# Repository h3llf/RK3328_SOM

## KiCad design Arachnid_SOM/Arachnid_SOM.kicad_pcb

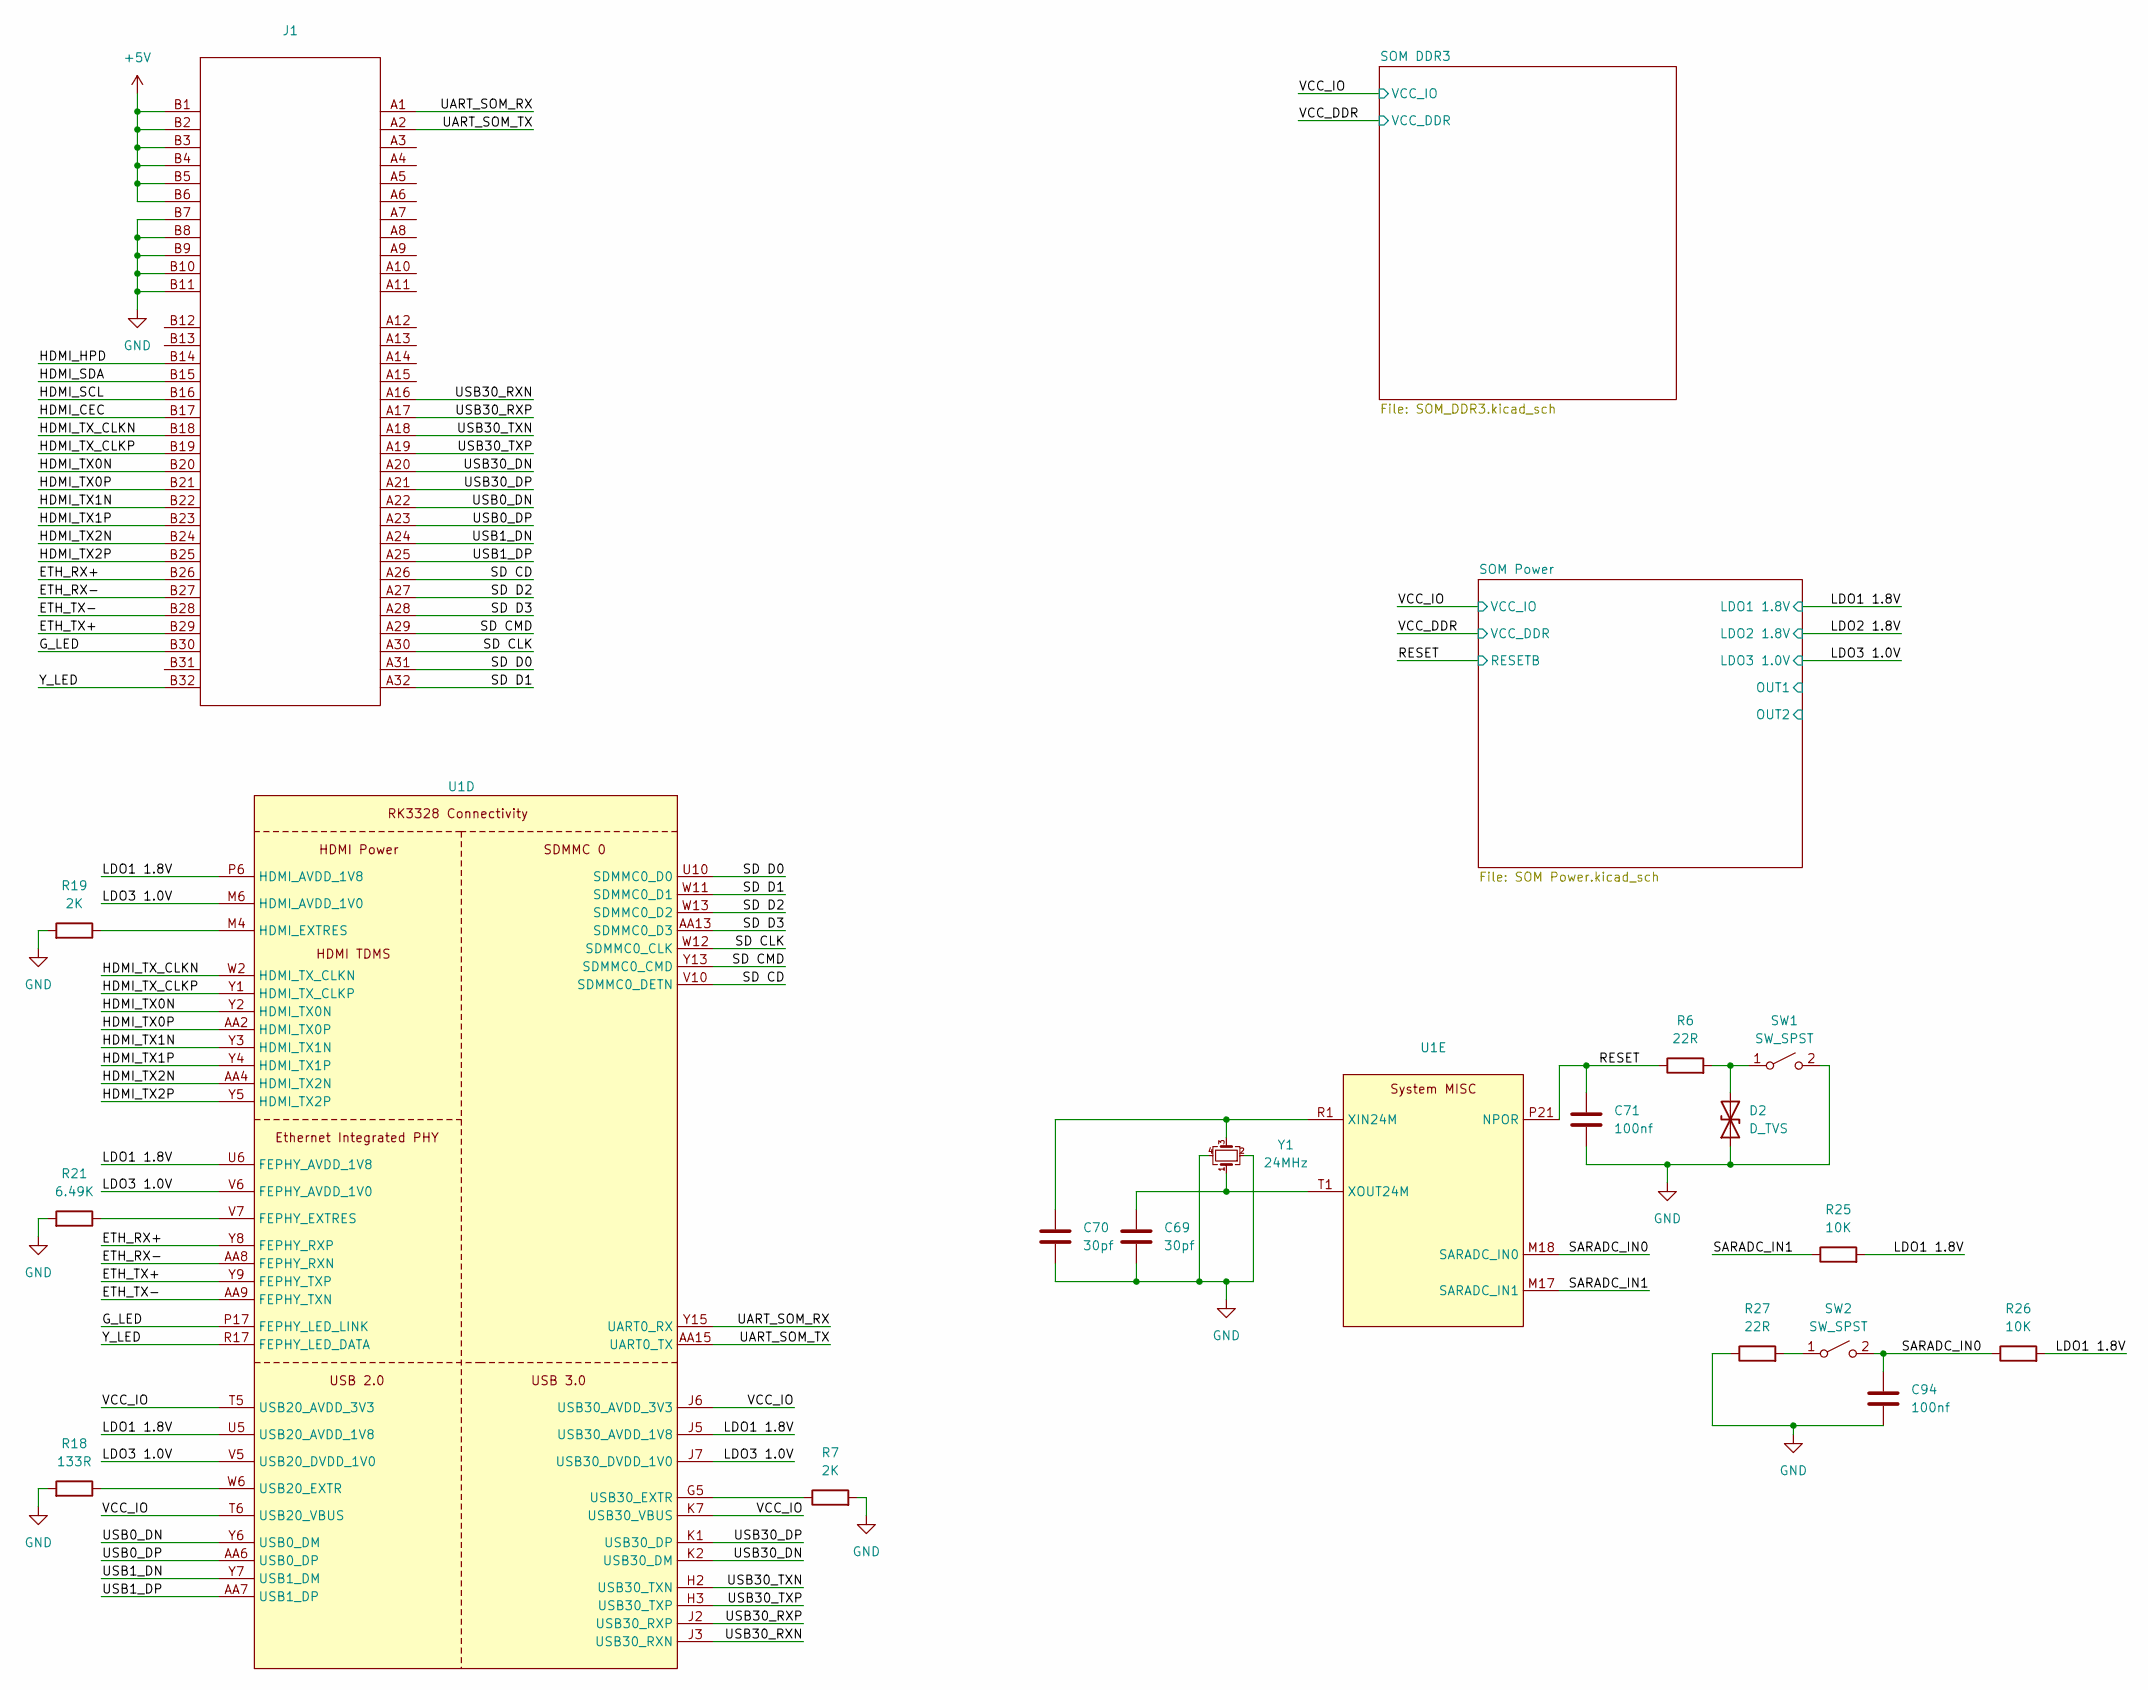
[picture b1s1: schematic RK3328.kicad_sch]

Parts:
C69, C70: 30pf; C_0402_1005Metric
C71, C94: 100nf; C_0402_1005Metric
D2: D_TVS; D_SOD-882
J1: BUS_PCIexpress_x4
R6, R27: 22R; R_0402_1005Metric
R7, R19: 2K; R_0402_1005Metric
R18: 133R; R_0402_1005Metric
R21: 6.49K; R_0402_1005Metric
R25, R26: 10K; R_0402_1005Metric
SW1, SW2: SW_SPST; SW_Push_1P1T_NO_Vertical_Wuerth_434133025816
U1: RK3328
Y1: 24MHz; Crystal_SMD_3225-4Pin_3.2x2.5mm; LCSC C70590

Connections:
+5V: J1.B1, J1.B2, J1.B3, J1.B4, J1.B5, J1.B6; also elsewhere on the board
/RK3328 SOM - DDR3 A/ETH_RX+: J1.B26, U1.Y8 (FEPHY_RXP)
/RK3328 SOM - DDR3 A/ETH_RX-: J1.B27, U1.AA8 (FEPHY_RXN)
/RK3328 SOM - DDR3 A/ETH_TX+: J1.B29, U1.Y9 (FEPHY_TXP)
/RK3328 SOM - DDR3 A/ETH_TX-: J1.B28, U1.AA9 (FEPHY_TXN)
/RK3328 SOM - DDR3 A/G_LED: J1.B30, U1.P17 (FEPHY_LED_LINK)
/RK3328 SOM - DDR3 A/HDMI_CEC: J1.B17
/RK3328 SOM - DDR3 A/HDMI_HPD: J1.B14
/RK3328 SOM - DDR3 A/HDMI_SCL: J1.B16
/RK3328 SOM - DDR3 A/HDMI_SDA: J1.B15
/RK3328 SOM - DDR3 A/HDMI_TX0N: J1.B20, U1.Y2 (HDMI_TX0N)
/RK3328 SOM - DDR3 A/HDMI_TX0P: J1.B21, U1.AA2 (HDMI_TX0P)
/RK3328 SOM - DDR3 A/HDMI_TX1N: J1.B22, U1.Y3 (HDMI_TX1N)
/RK3328 SOM - DDR3 A/HDMI_TX1P: J1.B23, U1.Y4 (HDMI_TX1P)
/RK3328 SOM - DDR3 A/HDMI_TX2N: J1.B24, U1.AA4 (HDMI_TX2N)
/RK3328 SOM - DDR3 A/HDMI_TX2P: J1.B25, U1.Y5 (HDMI_TX2P)
/RK3328 SOM - DDR3 A/HDMI_TX_CLKN: J1.B18, U1.W2 (HDMI_TX_CLKN)
/RK3328 SOM - DDR3 A/HDMI_TX_CLKP: J1.B19, U1.Y1 (HDMI_TX_CLKP)
/RK3328 SOM - DDR3 A/LDO1 1.8V: R25.2, R26.2, U1.J5 (USB30_AVDD_1V8), U1.P6 (HDMI_AVDD_1V8), U1.U5 (USB20_AVDD_1V8), U1.U6 (FEPHY_AVDD_1V8); also elsewhere on the board
/RK3328 SOM - DDR3 A/LDO3 1.0V: U1.J7 (USB30_DVDD_1V0), U1.M6 (HDMI_AVDD_1V0), U1.V5 (USB20_DVDD_1V0), U1.V6 (FEPHY_AVDD_1V0); also elsewhere on the board
/RK3328 SOM - DDR3 A/RESET: C71.1, R6.1, U1.P21 (NPOR)
/RK3328 SOM - DDR3 A/SARADC_IN0: C94.1, R26.1, SW2.2 (B), U1.M18 (SARADC_IN0)
/RK3328 SOM - DDR3 A/SARADC_IN1: R25.1, U1.M17 (SARADC_IN1)
/RK3328 SOM - DDR3 A/SD CD: J1.A26, U1.V10 (SDMMC0_DETN)
/RK3328 SOM - DDR3 A/SD CLK: J1.A30, U1.W12 (SDMMC0_CLK)
/RK3328 SOM - DDR3 A/SD CMD: J1.A29, U1.Y13 (SDMMC0_CMD)
/RK3328 SOM - DDR3 A/SD D0: J1.A31, U1.U10 (SDMMC0_D0)
/RK3328 SOM - DDR3 A/SD D1: J1.A32, U1.W11 (SDMMC0_D1)
/RK3328 SOM - DDR3 A/SD D2: J1.A27, U1.W13 (SDMMC0_D2)
/RK3328 SOM - DDR3 A/SD D3: J1.A28, U1.AA13 (SDMMC0_D3)
/RK3328 SOM - DDR3 A/UART_SOM_RX: J1.A1, U1.Y15 (UART0_RX)
/RK3328 SOM - DDR3 A/UART_SOM_TX: J1.A2, U1.AA15 (UART0_TX)
/RK3328 SOM - DDR3 A/USB0_DN: J1.A22, U1.Y6 (USB0_DM)
/RK3328 SOM - DDR3 A/USB0_DP: J1.A23, U1.AA6 (USB0_DP)
/RK3328 SOM - DDR3 A/USB1_DN: J1.A24, U1.Y7 (USB1_DM)
/RK3328 SOM - DDR3 A/USB1_DP: J1.A25, U1.AA7 (USB1_DP)
/RK3328 SOM - DDR3 A/USB30_DN: J1.A20, U1.K2 (USB30_DM)
/RK3328 SOM - DDR3 A/USB30_DP: J1.A21, U1.K1 (USB30_DP)
/RK3328 SOM - DDR3 A/USB30_RXN: J1.A16, U1.J3 (USB30_RXN)
/RK3328 SOM - DDR3 A/USB30_RXP: J1.A17, U1.J2 (USB30_RXP)
/RK3328 SOM - DDR3 A/USB30_TXN: J1.A18, U1.H2 (USB30_TXN)
/RK3328 SOM - DDR3 A/USB30_TXP: J1.A19, U1.H3 (USB30_TXP)
/RK3328 SOM - DDR3 A/VCC_IO: U1.J6 (USB30_AVDD_3V3), U1.K7 (USB30_VBUS), U1.T5 (USB20_AVDD_3V3), U1.T6 (USB20_VBUS); also elsewhere on the board
/RK3328 SOM - DDR3 A/Y_LED: J1.B32, U1.R17 (FEPHY_LED_DATA)
GND: C69.2, C70.2, C71.2, C94.2, D2.1 (A1), J1.B7, J1.B8, J1.B9, J1.B10, J1.B11, R7.2, R18.2, R19.2, R21.2, R27.1, SW1.2 (B), Y1.2, Y1.4; also elsewhere on the board
unnamed: D2.2 (A2), R6.2, SW1.1 (A)
unnamed: R27.2, SW2.1 (A)
unnamed: R21.1, U1.V7 (FEPHY_EXTRES)
unnamed: R19.1, U1.M4 (HDMI_EXTRES)
unnamed: R18.1, U1.W6 (USB20_EXTR)
unnamed: R7.1, U1.G5 (USB30_EXTR)
unnamed: C70.1, U1.R1 (XIN24M), Y1.3
unnamed: C69.1, U1.T1 (XOUT24M), Y1.1

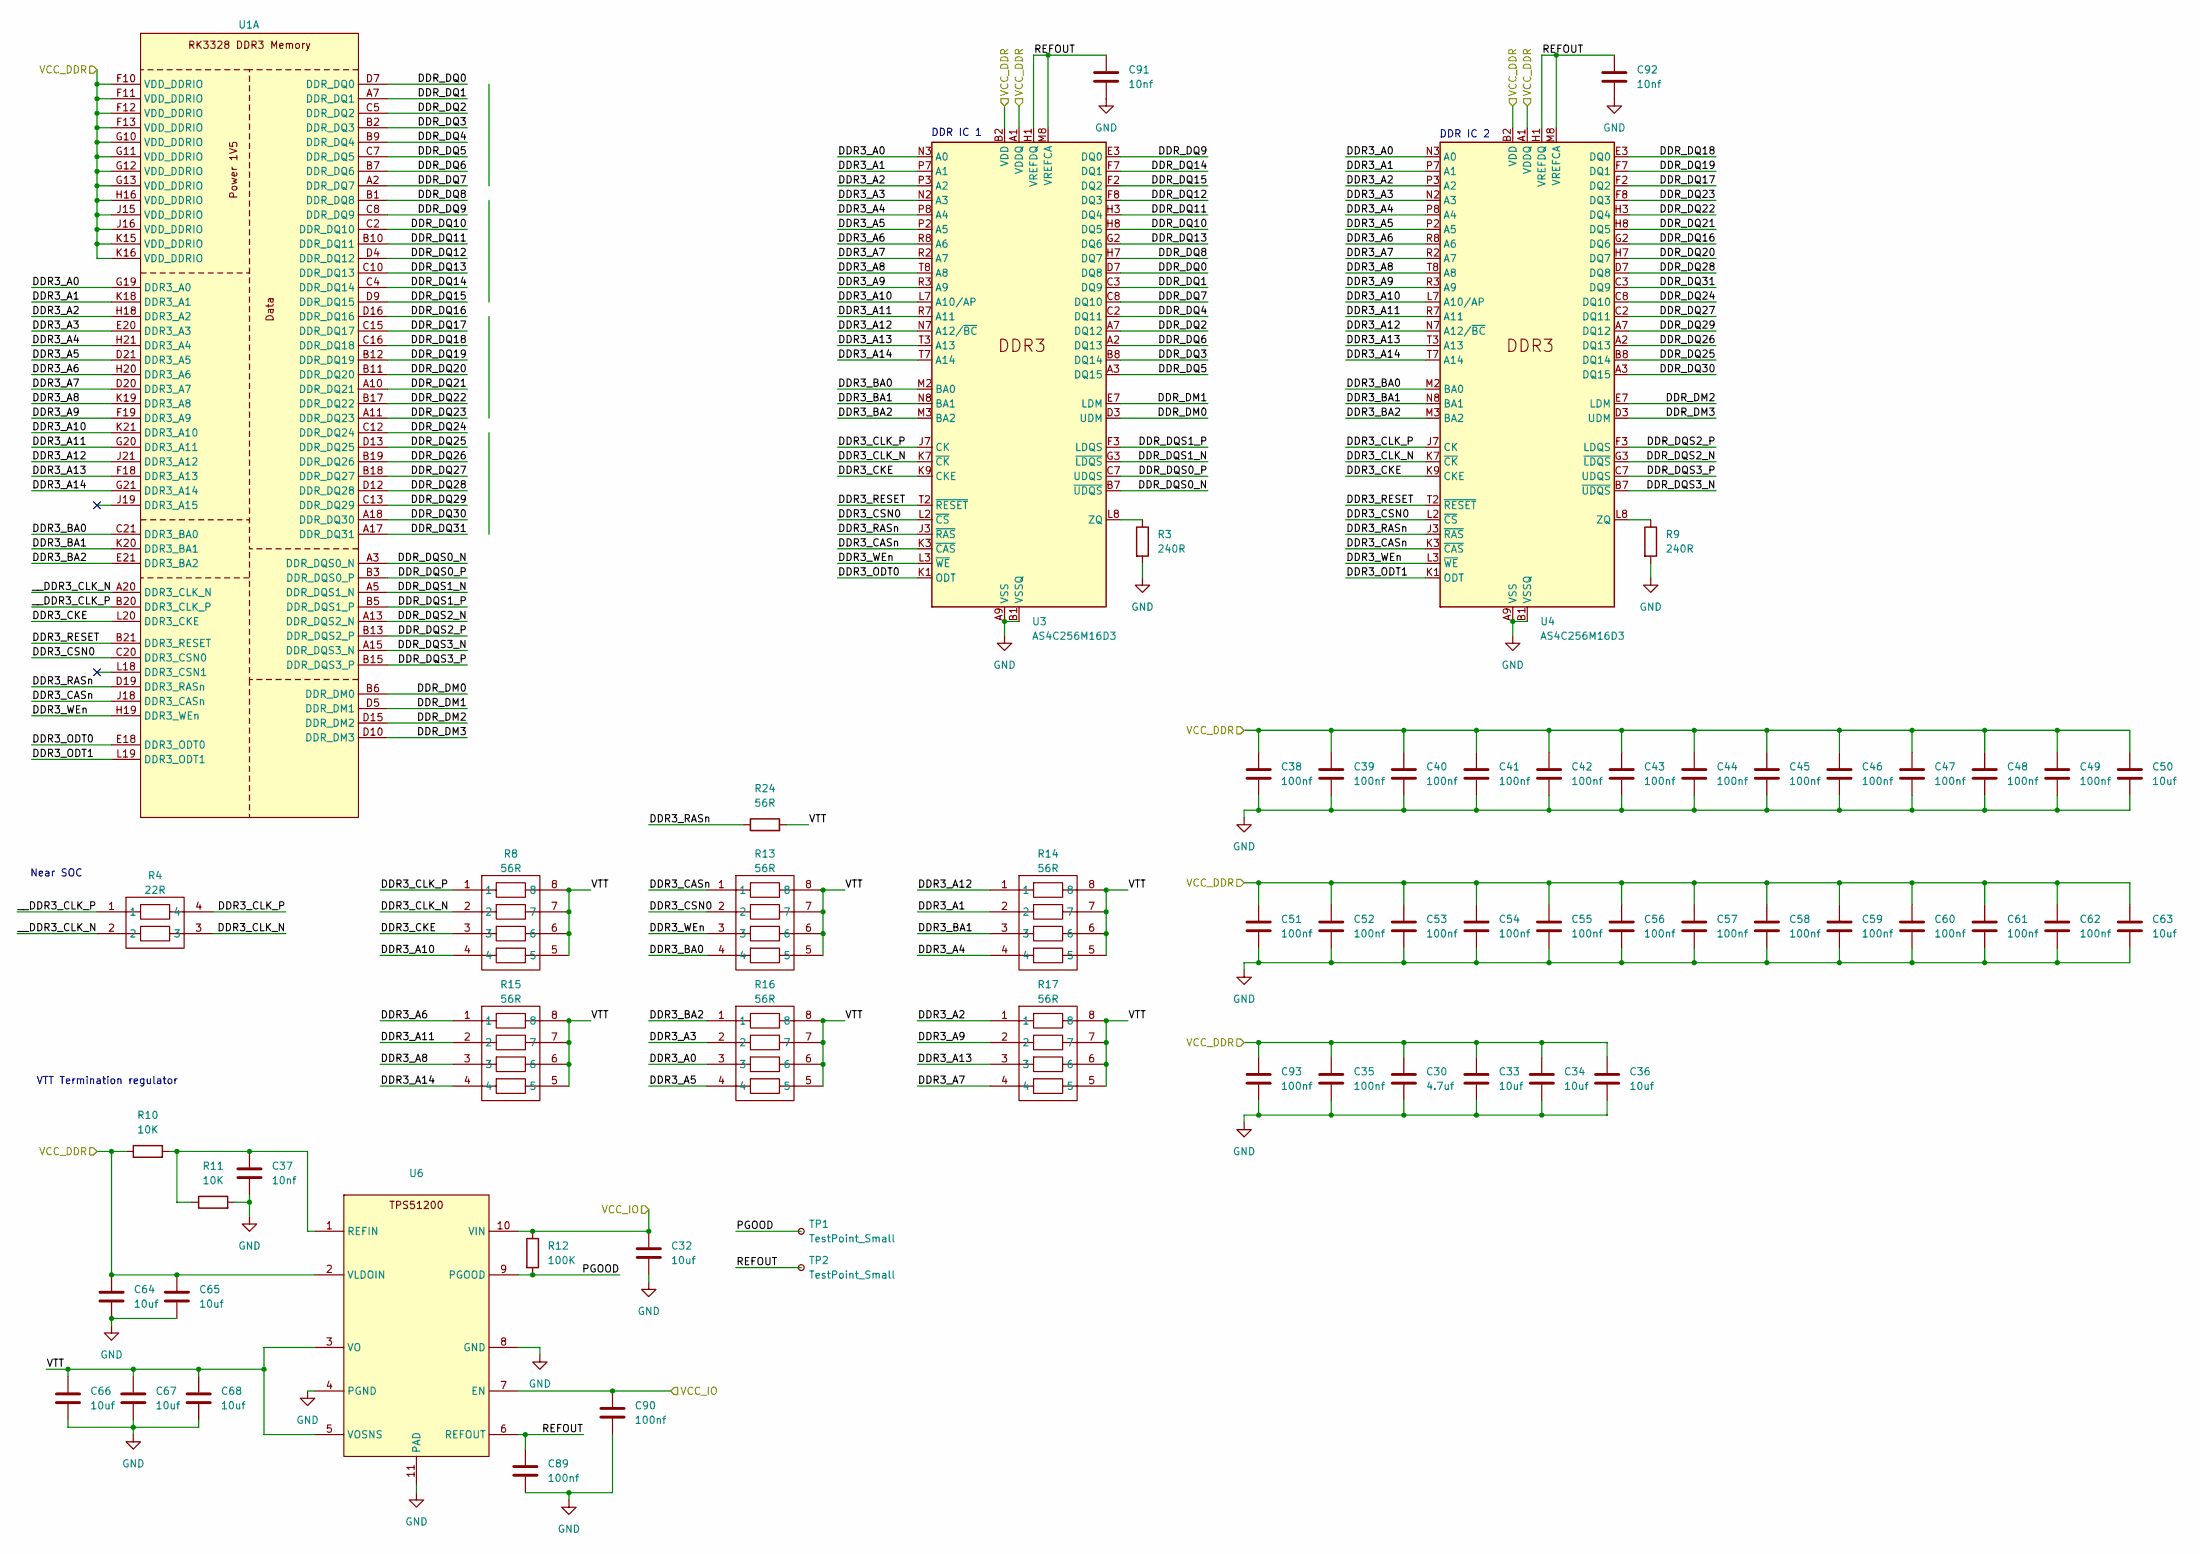
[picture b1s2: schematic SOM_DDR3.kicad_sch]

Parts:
C30: 4.7uf; C_0402_1005Metric
C32, C33, C34, C36, C50, C63, C64, C65, C66, C67, C68: 10uf; C_0402_1005Metric
C35, C38, C39, C40, C41, C42, C43, C44, C45, C46, C47, C48, C49, C51, C52, C53, C54, C55, C56, C57, C58, C59, C60, C61, C62, C89, C90, C93: 100nf; C_0402_1005Metric
C37, C91, C92: 10nf; C_0402_1005Metric
R3, R9: 240R; R_0402_1005Metric_Pad0.72x0.64mm_HandSolder
R4: 22R; R_Array_Convex_2x0402
R8, R13, R14, R15, R16, R17: 56R; R_Array_Convex_4x0402
R10, R11: 10K; R_0402_1005Metric
R12: 100K; R_0402_1005Metric
R24: 56R; R_0402_1005Metric
TP1, TP2: TestPoint_Small; TestPoint_Pad_D1.5mm
U1: RK3328
U3, U4: AS4C256M16D3; BGA-96_9.0x13.0mm_Layout2x3x16_P0.8mm
U6: VSON-10-1EP_3x3mm_P0.5mm_EP1.65x2.4mm_ThermalVias

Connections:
/RK3328 SOM - DDR3 A/SOM DDR3/DDR3_A0: R16.3, U1.G19 (DDR3_A0), U3.N3 (A0), U4.N3 (A0)
/RK3328 SOM - DDR3 A/SOM DDR3/DDR3_A1: R14.2, U1.K18 (DDR3_A1), U3.P7 (A1), U4.P7 (A1)
/RK3328 SOM - DDR3 A/SOM DDR3/DDR3_A2: R17.1, U1.H18 (DDR3_A2), U3.P3 (A2), U4.P3 (A2)
/RK3328 SOM - DDR3 A/SOM DDR3/DDR3_A3: R16.2, U1.E20 (DDR3_A3), U3.N2 (A3), U4.N2 (A3)
/RK3328 SOM - DDR3 A/SOM DDR3/DDR3_A4: R14.4, U1.H21 (DDR3_A4), U3.P8 (A4), U4.P8 (A4)
/RK3328 SOM - DDR3 A/SOM DDR3/DDR3_A5: R16.4, U1.D21 (DDR3_A5), U3.P2 (A5), U4.P2 (A5)
/RK3328 SOM - DDR3 A/SOM DDR3/DDR3_A6: R15.1, U1.H20 (DDR3_A6), U3.R8 (A6), U4.R8 (A6)
/RK3328 SOM - DDR3 A/SOM DDR3/DDR3_A7: R17.4, U1.D20 (DDR3_A7), U3.R2 (A7), U4.R2 (A7)
/RK3328 SOM - DDR3 A/SOM DDR3/DDR3_A8: R15.3, U1.K19 (DDR3_A8), U3.T8 (A8), U4.T8 (A8)
/RK3328 SOM - DDR3 A/SOM DDR3/DDR3_A9: R17.2, U1.F19 (DDR3_A9), U3.R3 (A9), U4.R3 (A9)
/RK3328 SOM - DDR3 A/SOM DDR3/DDR3_A10: R8.4, U1.K21 (DDR3_A10), U3.L7 (A10/AP), U4.L7 (A10/AP)
/RK3328 SOM - DDR3 A/SOM DDR3/DDR3_A11: R15.2, U1.G20 (DDR3_A11), U3.R7 (A11), U4.R7 (A11)
/RK3328 SOM - DDR3 A/SOM DDR3/DDR3_A12: R14.1, U1.J21 (DDR3_A12), U3.N7 (A12/~BC), U4.N7 (A12/~BC)
/RK3328 SOM - DDR3 A/SOM DDR3/DDR3_A13: R17.3, U1.F18 (DDR3_A13), U3.T3 (A13), U4.T3 (A13)
/RK3328 SOM - DDR3 A/SOM DDR3/DDR3_A14: R15.4, U1.G21 (DDR3_A14), U3.T7 (A14), U4.T7 (A14)
/RK3328 SOM - DDR3 A/SOM DDR3/DDR3_BA0: R13.4, U1.C21 (DDR3_BA0), U3.M2 (BA0), U4.M2 (BA0)
/RK3328 SOM - DDR3 A/SOM DDR3/DDR3_BA1: R14.3, U1.K20 (DDR3_BA1), U3.N8 (BA1), U4.N8 (BA1)
/RK3328 SOM - DDR3 A/SOM DDR3/DDR3_BA2: R16.1, U1.E21 (DDR3_BA2), U3.M3 (BA2), U4.M3 (BA2)
/RK3328 SOM - DDR3 A/SOM DDR3/DDR3_CASn: R13.1, U1.J18 (DDR3_CASn), U3.K3 (~CAS), U4.K3 (~CAS)
/RK3328 SOM - DDR3 A/SOM DDR3/DDR3_CKE: R8.3, U1.L20 (DDR3_CKE), U3.K9 (CKE), U4.K9 (CKE)
/RK3328 SOM - DDR3 A/SOM DDR3/DDR3_CLK_N: R4.3, R8.2, U3.K7 (~CK), U4.K7 (~CK)
/RK3328 SOM - DDR3 A/SOM DDR3/DDR3_CLK_P: R4.4, R8.1, U3.J7 (CK), U4.J7 (CK)
/RK3328 SOM - DDR3 A/SOM DDR3/DDR3_CSN0: R13.2, U1.C20 (DDR3_CSN0), U3.L2 (~CS), U4.L2 (~CS)
/RK3328 SOM - DDR3 A/SOM DDR3/DDR3_ODT0: U1.E18 (DDR3_ODT0), U3.K1 (ODT)
/RK3328 SOM - DDR3 A/SOM DDR3/DDR3_ODT1: U1.L19 (DDR3_ODT1), U4.K1 (ODT)
/RK3328 SOM - DDR3 A/SOM DDR3/DDR3_RASn: R24.1, U1.D19 (DDR3_RASn), U3.J3 (~RAS), U4.J3 (~RAS)
/RK3328 SOM - DDR3 A/SOM DDR3/DDR3_RESET: U1.B21 (DDR3_RESET), U3.T2 (~RESET), U4.T2 (~RESET)
/RK3328 SOM - DDR3 A/SOM DDR3/DDR3_WEn: R13.3, U1.H19 (DDR3_WEn), U3.L3 (~WE), U4.L3 (~WE)
/RK3328 SOM - DDR3 A/SOM DDR3/DDR_DM0: U1.B6 (DDR_DM0), U3.D3 (UDM)
/RK3328 SOM - DDR3 A/SOM DDR3/DDR_DM1: U1.D5 (DDR_DM1), U3.E7 (LDM)
/RK3328 SOM - DDR3 A/SOM DDR3/DDR_DM2: U1.D15 (DDR_DM2), U4.E7 (LDM)
/RK3328 SOM - DDR3 A/SOM DDR3/DDR_DM3: U1.D10 (DDR_DM3), U4.D3 (UDM)
/RK3328 SOM - DDR3 A/SOM DDR3/DDR_DQ0: U1.D7 (DDR_DQ0), U3.D7 (DQ8)
/RK3328 SOM - DDR3 A/SOM DDR3/DDR_DQ1: U1.A7 (DDR_DQ1), U3.C3 (DQ9)
/RK3328 SOM - DDR3 A/SOM DDR3/DDR_DQ2: U1.C5 (DDR_DQ2), U3.A7 (DQ12)
/RK3328 SOM - DDR3 A/SOM DDR3/DDR_DQ3: U1.B2 (DDR_DQ3), U3.B8 (DQ14)
/RK3328 SOM - DDR3 A/SOM DDR3/DDR_DQ4: U1.B9 (DDR_DQ4), U3.C2 (DQ11)
/RK3328 SOM - DDR3 A/SOM DDR3/DDR_DQ5: U1.C7 (DDR_DQ5), U3.A3 (DQ15)
/RK3328 SOM - DDR3 A/SOM DDR3/DDR_DQ6: U1.B7 (DDR_DQ6), U3.A2 (DQ13)
/RK3328 SOM - DDR3 A/SOM DDR3/DDR_DQ7: U1.A2 (DDR_DQ7), U3.C8 (DQ10)
/RK3328 SOM - DDR3 A/SOM DDR3/DDR_DQ8: U1.B1 (DDR_DQ8), U3.H7 (DQ7)
/RK3328 SOM - DDR3 A/SOM DDR3/DDR_DQ9: U1.C8 (DDR_DQ9), U3.E3 (DQ0)
/RK3328 SOM - DDR3 A/SOM DDR3/DDR_DQ10: U1.C2 (DDR_DQ10), U3.H8 (DQ5)
/RK3328 SOM - DDR3 A/SOM DDR3/DDR_DQ11: U1.B10 (DDR_DQ11), U3.H3 (DQ4)
/RK3328 SOM - DDR3 A/SOM DDR3/DDR_DQ12: U1.D4 (DDR_DQ12), U3.F8 (DQ3)
/RK3328 SOM - DDR3 A/SOM DDR3/DDR_DQ13: U1.C10 (DDR_DQ13), U3.G2 (DQ6)
/RK3328 SOM - DDR3 A/SOM DDR3/DDR_DQ14: U1.C4 (DDR_DQ14), U3.F7 (DQ1)
/RK3328 SOM - DDR3 A/SOM DDR3/DDR_DQ15: U1.D9 (DDR_DQ15), U3.F2 (DQ2)
/RK3328 SOM - DDR3 A/SOM DDR3/DDR_DQ16: U1.D16 (DDR_DQ16), U4.G2 (DQ6)
/RK3328 SOM - DDR3 A/SOM DDR3/DDR_DQ17: U1.C15 (DDR_DQ17), U4.F2 (DQ2)
/RK3328 SOM - DDR3 A/SOM DDR3/DDR_DQ18: U1.C16 (DDR_DQ18), U4.E3 (DQ0)
/RK3328 SOM - DDR3 A/SOM DDR3/DDR_DQ19: U1.B12 (DDR_DQ19), U4.F7 (DQ1)
/RK3328 SOM - DDR3 A/SOM DDR3/DDR_DQ20: U1.B11 (DDR_DQ20), U4.H7 (DQ7)
/RK3328 SOM - DDR3 A/SOM DDR3/DDR_DQ21: U1.A10 (DDR_DQ21), U4.H8 (DQ5)
/RK3328 SOM - DDR3 A/SOM DDR3/DDR_DQ22: U1.B17 (DDR_DQ22), U4.H3 (DQ4)
/RK3328 SOM - DDR3 A/SOM DDR3/DDR_DQ23: U1.A11 (DDR_DQ23), U4.F8 (DQ3)
/RK3328 SOM - DDR3 A/SOM DDR3/DDR_DQ24: U1.C12 (DDR_DQ24), U4.C8 (DQ10)
/RK3328 SOM - DDR3 A/SOM DDR3/DDR_DQ25: U1.D13 (DDR_DQ25), U4.B8 (DQ14)
/RK3328 SOM - DDR3 A/SOM DDR3/DDR_DQ26: U1.B19 (DDR_DQ26), U4.A2 (DQ13)
/RK3328 SOM - DDR3 A/SOM DDR3/DDR_DQ27: U1.B18 (DDR_DQ27), U4.C2 (DQ11)
/RK3328 SOM - DDR3 A/SOM DDR3/DDR_DQ28: U1.D12 (DDR_DQ28), U4.D7 (DQ8)
/RK3328 SOM - DDR3 A/SOM DDR3/DDR_DQ29: U1.C13 (DDR_DQ29), U4.A7 (DQ12)
/RK3328 SOM - DDR3 A/SOM DDR3/DDR_DQ30: U1.A18 (DDR_DQ30), U4.A3 (DQ15)
/RK3328 SOM - DDR3 A/SOM DDR3/DDR_DQ31: U1.A17 (DDR_DQ31), U4.C3 (DQ9)
/RK3328 SOM - DDR3 A/SOM DDR3/DDR_DQS0_N: U1.A3 (DDR_DQS0_N), U3.B7 (~UDQS)
/RK3328 SOM - DDR3 A/SOM DDR3/DDR_DQS0_P: U1.B3 (DDR_DQS0_P), U3.C7 (UDQS)
/RK3328 SOM - DDR3 A/SOM DDR3/DDR_DQS1_N: U1.A5 (DDR_DQS1_N), U3.G3 (~LDQS)
/RK3328 SOM - DDR3 A/SOM DDR3/DDR_DQS1_P: U1.B5 (DDR_DQS1_P), U3.F3 (LDQS)
/RK3328 SOM - DDR3 A/SOM DDR3/DDR_DQS2_N: U1.A13 (DDR_DQS2_N), U4.G3 (~LDQS)
/RK3328 SOM - DDR3 A/SOM DDR3/DDR_DQS2_P: U1.B13 (DDR_DQS2_P), U4.F3 (LDQS)
/RK3328 SOM - DDR3 A/SOM DDR3/DDR_DQS3_N: U1.A15 (DDR_DQS3_N), U4.B7 (~UDQS)
/RK3328 SOM - DDR3 A/SOM DDR3/DDR_DQS3_P: U1.B15 (DDR_DQS3_P), U4.C7 (UDQS)
/RK3328 SOM - DDR3 A/SOM DDR3/PGOOD: R12.2, TP1.1, U6.9 (PGOOD)
/RK3328 SOM - DDR3 A/SOM DDR3/REFOUT: C89.1, C91.1, C92.1, TP2.1, U3.H1 (VREFDQ), U3.M8 (VREFCA), U4.H1 (VREFDQ), U4.M8 (VREFCA), U6.6 (REFOUT)
/RK3328 SOM - DDR3 A/SOM DDR3/VTT: C66.1, C67.1, C68.1, R8.5, R8.6, R8.7, R8.8, R13.5, R13.6, R13.7, R13.8, R14.5, R14.6, R14.7, R14.8, R15.5, R15.6, R15.7, R15.8, R16.5, R16.6, R16.7, R16.8, R17.5, R17.6, R17.7, R17.8, R24.2, U6.3 (VO), U6.5 (VOSNS)
/RK3328 SOM - DDR3 A/SOM DDR3/__DDR3_CLK_N: R4.2, U1.A20 (DDR3_CLK_N)
/RK3328 SOM - DDR3 A/SOM DDR3/__DDR3_CLK_P: R4.1, U1.B20 (DDR3_CLK_P)
/RK3328 SOM - DDR3 A/VCC_DDR: C30.1, C33.1, C34.1, C35.1, C36.1, C38.1, C39.1, C40.1, C41.1, C42.1, C43.1, C44.1, C45.1, C46.1, C47.1, C48.1, C49.1, C50.1, C51.1, C52.1, C53.1, C54.1, C55.1, C56.1, C57.1, C58.1, C59.1, C60.1, C61.1, C62.1, C63.1, C64.1, C65.1, C93.1, R10.1, U1.F10 (VDD_DDRIO), U1.F11 (VDD_DDRIO), U1.F12 (VDD_DDRIO), U1.F13 (VDD_DDRIO), U1.G10 (VDD_DDRIO), U1.G11 (VDD_DDRIO), U1.G12 (VDD_DDRIO), U1.G13 (VDD_DDRIO), U1.H16 (VDD_DDRIO), U1.J15 (VDD_DDRIO), U1.J16 (VDD_DDRIO), U1.K15 (VDD_DDRIO), U1.K16 (VDD_DDRIO), U3.A1 (VDDQ), U3.A8 (VDDQ), U3.B2 (VDD), U3.C1 (VDDQ), U3.C9 (VDDQ), U3.D2 (VDDQ), U3.D9 (VDD), U3.E9 (VDDQ), U3.F1 (VDDQ), U3.G7 (VDD), U3.H2 (VDDQ), U3.H9 (VDDQ), U3.K2 (VDD), U3.K8 (VDD), U3.N1 (VDD), U3.N9 (VDD), U3.R1 (VDD), U3.R9 (VDD), U4.A1 (VDDQ), U4.A8 (VDDQ), U4.B2 (VDD), U4.C1 (VDDQ), U4.C9 (VDDQ), U4.D2 (VDDQ), U4.D9 (VDD), U4.E9 (VDDQ), U4.F1 (VDDQ), U4.G7 (VDD), U4.H2 (VDDQ), U4.H9 (VDDQ), U4.K2 (VDD), U4.K8 (VDD), U4.N1 (VDD), U4.N9 (VDD), U4.R1 (VDD), U4.R9 (VDD), U6.2 (VLDOIN); also elsewhere on the board
/RK3328 SOM - DDR3 A/VCC_IO: C32.1, C90.1, R12.1, U6.7 (EN), U6.10 (VIN); also elsewhere on the board
GND: C30.2, C32.2, C33.2, C34.2, C35.2, C36.2, C37.2, C38.2, C39.2, C40.2, C41.2, C42.2, C43.2, C44.2, C45.2, C46.2, C47.2, C48.2, C49.2, C50.2, C51.2, C52.2, C53.2, C54.2, C55.2, C56.2, C57.2, C58.2, C59.2, C60.2, C61.2, C62.2, C63.2, C64.2, C65.2, C66.2, C67.2, C68.2, C89.2, C90.2, C91.2, C92.2, C93.2, R3.2, R9.2, R11.2, U3.A9 (VSS), U3.B1 (VSSQ), U3.B3 (VSS), U3.B9 (VSSQ), U3.D1 (VSSQ), U3.D8 (VSSQ), U3.E1 (VSS), U3.E2 (VSSQ), U3.E8 (VSSQ), U3.F9 (VSSQ), U3.G1 (VSSQ), U3.G8 (VSS), U3.G9 (VSSQ), U3.J2 (VSS), U3.J8 (VSS), U3.M1 (VSS), U3.M9 (VSS), U3.P1 (VSS), U3.P9 (VSS), U3.T1 (VSS), U3.T9 (VSS), U4.A9 (VSS), U4.B1 (VSSQ), U4.B3 (VSS), U4.B9 (VSSQ), U4.D1 (VSSQ), U4.D8 (VSSQ), U4.E1 (VSS), U4.E2 (VSSQ), U4.E8 (VSSQ), U4.F9 (VSSQ), U4.G1 (VSSQ), U4.G8 (VSS), U4.G9 (VSSQ), U4.J2 (VSS), U4.J8 (VSS), U4.M1 (VSS), U4.M9 (VSS), U4.P1 (VSS), U4.P9 (VSS), U4.T1 (VSS), U4.T9 (VSS), U6.4 (PGND), U6.8 (GND), U6.11 (PAD); also elsewhere on the board
unnamed: R3.1, U3.L8 (ZQ)
unnamed: R9.1, U4.L8 (ZQ)
unnamed: C37.1, R10.2, R11.1, U6.1 (REFIN)

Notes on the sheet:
Near SOC
DDR IC 1
DDR IC 2
VTT Termination regulator

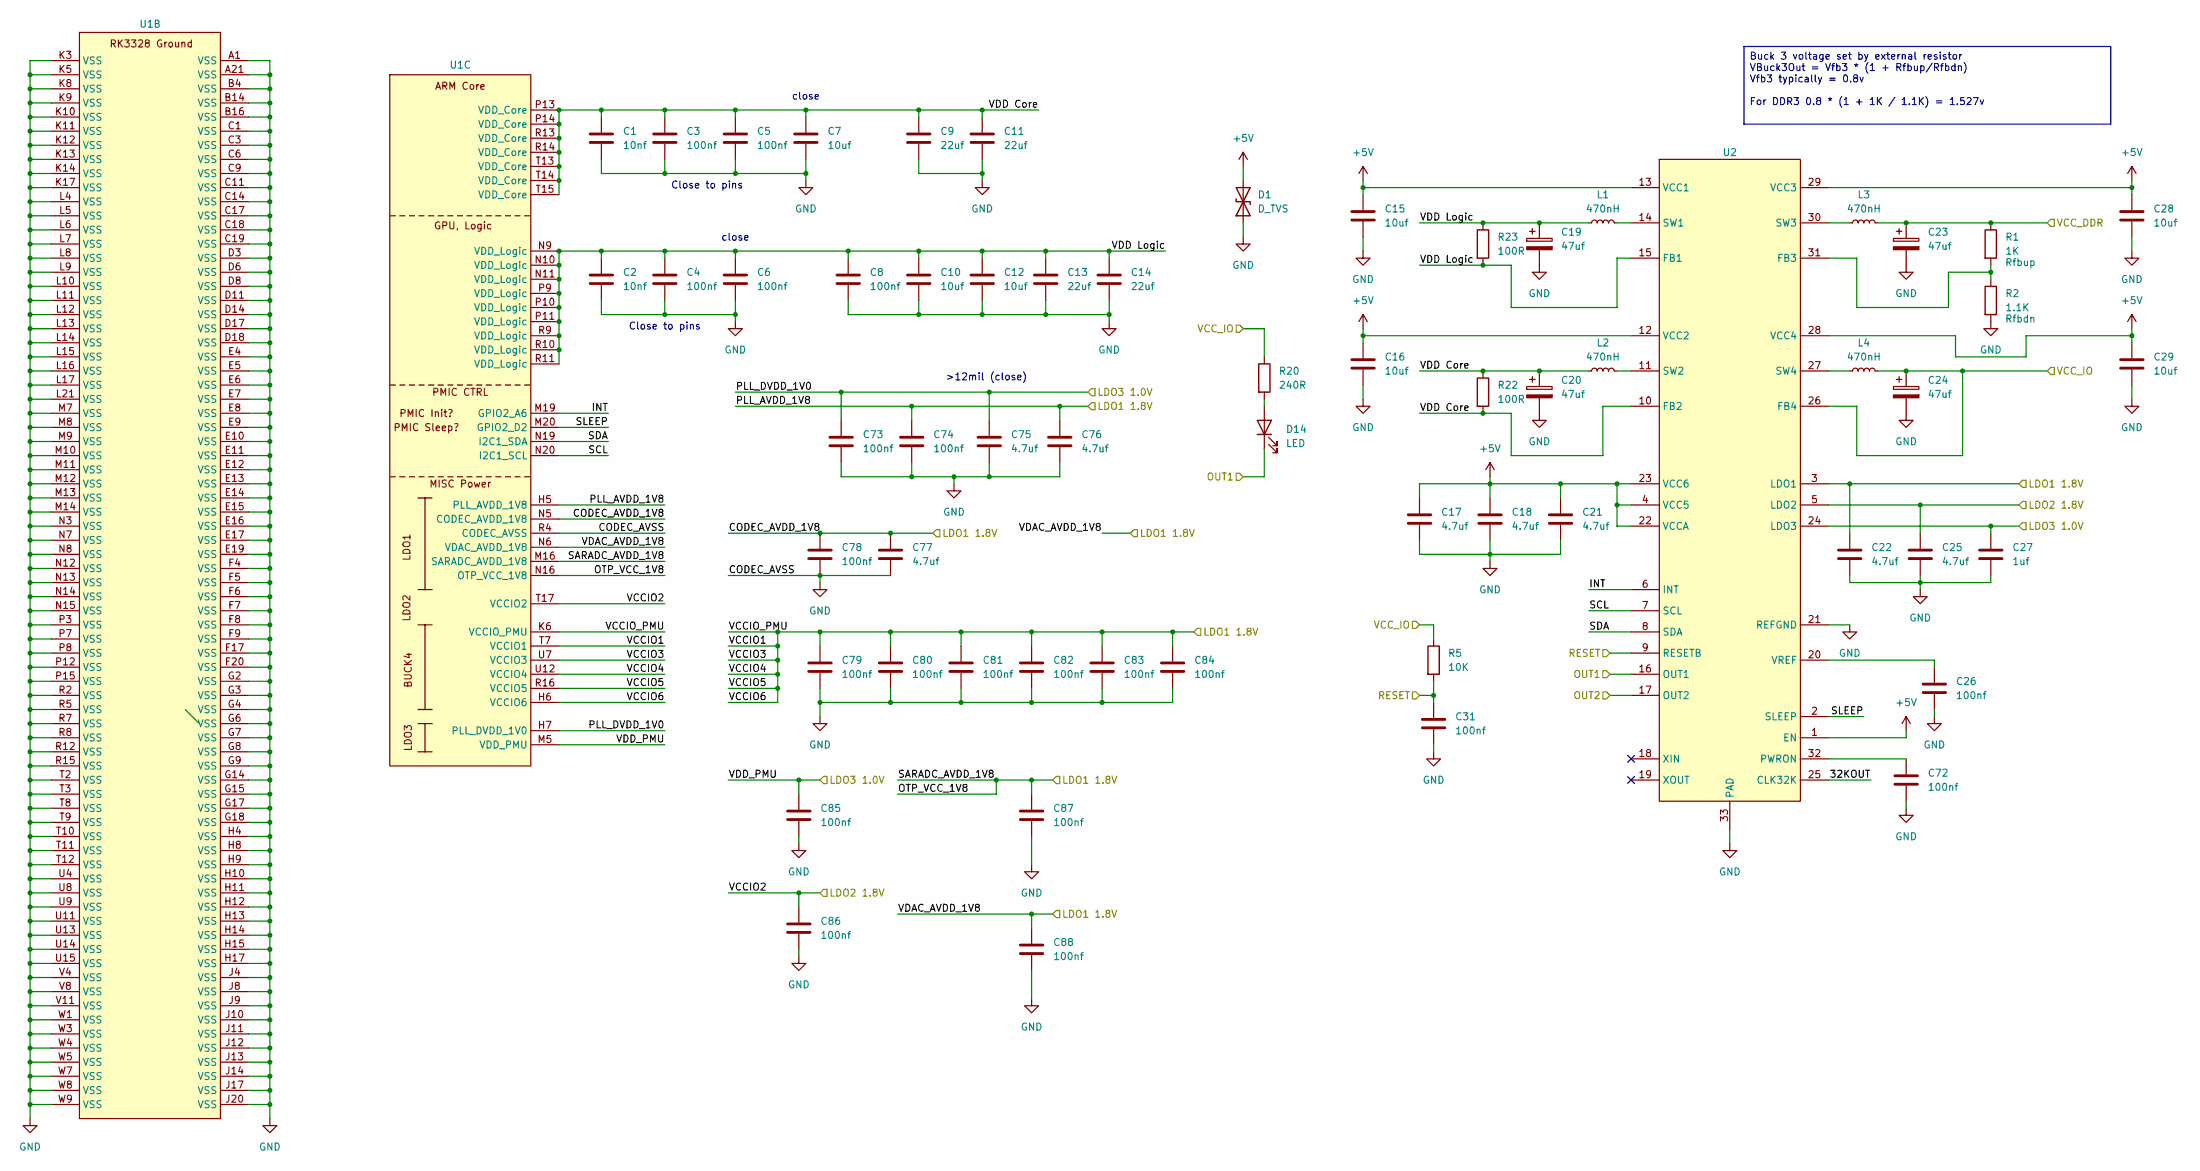
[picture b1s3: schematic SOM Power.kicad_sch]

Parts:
C1, C2: 10nf; C_0402_1005Metric_Pad0.74x0.62mm_HandSolder
C3, C4, C5, C6, C8, C85, C87: 100nf; C_0402_1005Metric_Pad0.74x0.62mm_HandSolder
C7, C10, C12: 10uf; C_0402_1005Metric_Pad0.74x0.62mm_HandSolder
C9, C11, C13, C14: 22uf; C_0603_1608Metric_Pad1.08x0.95mm_HandSolder
C15, C16, C28, C29: 10uf; C_0603_1608Metric
C17, C18, C21, C22, C25, C77: 4.7uf; C_0402_1005Metric
C19, C20, C23, C24: 47uf; CP_EIA-3528-21_Kemet-B
C26, C31, C72, C73, C74, C78, C79, C80, C81, C82, C83, C84, C86, C88: 100nf; C_0402_1005Metric
C27: 1uf; C_0402_1005Metric
C75, C76: 4.7uf; C_0603_1608Metric
D1: D_TVS; D_SOD-882
D14: LED; LED_0603_1608Metric
L1, L2, L3, L4: 470nH; L_Cenker_CKCS201610
R1: 1K; R_0603_1608Metric
R2: 1.1K; R_0603_1608Metric
R5: 10K; R_0402_1005Metric
R20: 240R; R_0402_1005Metric
R22, R23: 100R; R_0402_1005Metric
U1: RK3328
U2: QFN-32-1EP_4x4mm_P0.4mm_EP2.65x2.65mm

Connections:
+5V: C15.1, C16.1, C17.1, C18.1, C21.2, C28.1, C29.1, D1.2 (A2), U2.1 (EN), U2.4 (VCC5), U2.12 (VCC2), U2.13 (VCC1), U2.22 (VCCA), U2.23 (VCC6), U2.28 (VCC4), U2.29 (VCC3); also elsewhere on the board
/RK3328 SOM - DDR3 A/LDO1 1.8V: C22.1, C74.1, C76.1, C77.1, C78.1, C79.1, C80.1, C81.1, C82.1, C83.1, C84.1, C87.1, C88.1, U1.H5 (PLL_AVDD_1V8), U1.H6 (VCCIO6), U1.K6 (VCCIO_PMU), U1.M16 (SARADC_AVDD_1V8), U1.N5 (CODEC_AVDD_1V8), U1.N6 (VDAC_AVDD_1V8), U1.N16 (OTP_VCC_1V8), U1.R16 (VCCIO5), U1.T7 (VCCIO1), U1.U7 (VCCIO3), U1.U12 (VCCIO4), U2.3 (LDO1); also elsewhere on the board
/RK3328 SOM - DDR3 A/LDO2 1.8V: C25.1, C86.1, U1.T17 (VCCIO2), U2.5 (LDO2)
/RK3328 SOM - DDR3 A/LDO3 1.0V: C27.1, C73.1, C75.1, C85.1, U1.H7 (PLL_DVDD_1V0), U1.M5 (VDD_PMU), U2.24 (LDO3); also elsewhere on the board
/RK3328 SOM - DDR3 A/SOM Power/32KOUT: U2.25 (CLK32K)
/RK3328 SOM - DDR3 A/SOM Power/INT: U1.M19 (GPIO2_A6), U2.6 (INT)
/RK3328 SOM - DDR3 A/SOM Power/OUT1: D14.1 (K), U2.16 (OUT1)
/RK3328 SOM - DDR3 A/SOM Power/OUT2: U2.17 (OUT2)
/RK3328 SOM - DDR3 A/SOM Power/RESET: C31.1, R5.2, U2.9 (RESETB)
/RK3328 SOM - DDR3 A/SOM Power/SCL: U1.N20 (I2C1_SCL), U2.7 (SCL)
/RK3328 SOM - DDR3 A/SOM Power/SDA: U1.N19 (I2C1_SDA), U2.8 (SDA)
/RK3328 SOM - DDR3 A/SOM Power/SLEEP: U1.M20 (GPIO2_D2), U2.2 (SLEEP)
/RK3328 SOM - DDR3 A/SOM Power/VDD Core: C1.1, C3.1, C5.1, C7.1, C9.1, C11.1, C20.1, L2.1, R22.1, R22.2, U1.P13 (VDD_Core), U1.P14 (VDD_Core), U1.R13 (VDD_Core), U1.R14 (VDD_Core), U1.T13 (VDD_Core), U1.T14 (VDD_Core), U1.T15 (VDD_Core), U2.10 (FB2)
/RK3328 SOM - DDR3 A/SOM Power/VDD Logic: C2.1, C4.1, C6.1, C8.1, C10.1, C12.1, C13.1, C14.1, C19.1, L1.1, R23.1, R23.2, U1.N9 (VDD_Logic), U1.N10 (VDD_Logic), U1.N11 (VDD_Logic), U1.P9 (VDD_Logic), U1.P10 (VDD_Logic), U1.P11 (VDD_Logic), U1.R9 (VDD_Logic), U1.R10 (VDD_Logic), U1.R11 (VDD_Logic), U2.15 (FB1)
/RK3328 SOM - DDR3 A/VCC_DDR: C23.1, L3.2, R1.1; also elsewhere on the board
/RK3328 SOM - DDR3 A/VCC_IO: C24.1, L4.2, R5.1, R20.1, U2.26 (FB4); also elsewhere on the board
GND: C1.2, C2.2, C3.2, C4.2, C5.2, C6.2, C7.2, C8.2, C9.2, C10.2, C11.2, C12.2, C13.2, C14.2, C15.2, C16.2, C17.2, C18.2, C19.2, C20.2, C21.1, C22.2, C23.2, C24.2, C25.2, C26.2, C27.2, C28.2, C29.2, C31.2, C72.2, C73.2, C74.2, C75.2, C76.2, C77.2, C78.2, C79.2, C80.2, C81.2, C82.2, C83.2, C84.2, C85.2, C86.2, C87.2, C88.2, D1.1 (A1), R2.2, U1.A1 (VSS), U1.A21 (VSS), U1.B4 (VSS), U1.B14 (VSS), U1.B16 (VSS), U1.C1 (VSS), U1.C3 (VSS), U1.C6 (VSS), U1.C9 (VSS), U1.C11 (VSS), U1.C14 (VSS), U1.C17 (VSS), U1.C18 (VSS), U1.C19 (VSS), U1.D3 (VSS), U1.D6 (VSS), U1.D8 (VSS), U1.D11 (VSS), U1.D14 (VSS), U1.D17 (VSS), U1.D18 (VSS), U1.E4 (VSS), U1.E5 (VSS), U1.E6 (VSS), U1.E7 (VSS), U1.E8 (VSS), U1.E9 (VSS), U1.E10 (VSS), U1.E11 (VSS), U1.E12 (VSS), U1.E13 (VSS), U1.E14 (VSS), U1.E15 (VSS), U1.E16 (VSS), U1.E17 (VSS), U1.E19 (VSS), U1.F4 (VSS), U1.F5 (VSS), U1.F6 (VSS), U1.F7 (VSS), U1.F8 (VSS), U1.F9 (VSS), U1.F17 (VSS), U1.F20 (VSS), U1.G2 (VSS), U1.G3 (VSS), U1.G4 (VSS), U1.G6 (VSS), U1.G7 (VSS), U1.G8 (VSS), U1.G9 (VSS), U1.G14 (VSS), U1.G15 (VSS), U1.G17 (VSS), U1.G18 (VSS), U1.H4 (VSS), U1.H8 (VSS), U1.H9 (VSS), U1.H10 (VSS), U1.H11 (VSS), U1.H12 (VSS), U1.H13 (VSS), U1.H14 (VSS), U1.H15 (VSS), U1.H17 (VSS), U1.J4 (VSS), U1.J8 (VSS), U1.J9 (VSS), U1.J10 (VSS), U1.J11 (VSS), U1.J12 (VSS), U1.J13 (VSS), U1.J14 (VSS), U1.J17 (VSS), U1.J20 (VSS), U1.K3 (VSS), U1.K5 (VSS), U1.K8 (VSS), U1.K9 (VSS), U1.K10 (VSS), U1.K11 (VSS), U1.K12 (VSS), U1.K13 (VSS), U1.K14 (VSS), U1.K17 (VSS), U1.L4 (VSS), U1.L5 (VSS), U1.L6 (VSS), U1.L7 (VSS), U1.L8 (VSS), U1.L9 (VSS), U1.L10 (VSS), U1.L11 (VSS), U1.L12 (VSS), U1.L13 (VSS), U1.L14 (VSS), U1.L15 (VSS), U1.L16 (VSS), U1.L17 (VSS), U1.L21 (VSS), U1.M7 (VSS), U1.M8 (VSS), U1.M9 (VSS), U1.M10 (VSS), U1.M11 (VSS), U1.M12 (VSS), U1.M13 (VSS), U1.M14 (VSS), U1.N3 (VSS), U1.N7 (VSS), U1.N8 (VSS), U1.N12 (VSS), U1.N13 (VSS), U1.N14 (VSS), U1.N15 (VSS), U1.P3 (VSS), U1.P7 (VSS), U1.P8 (VSS), U1.P12 (VSS), U1.P15 (VSS), U1.R2 (VSS), U1.R4 (CODEC_AVSS), U1.R5 (VSS), U1.R7 (VSS), U1.R8 (VSS), U1.R12 (VSS), U1.R15 (VSS), U1.T2 (VSS), U1.T3 (VSS), U1.T8 (VSS), U1.T9 (VSS), U1.T10 (VSS), U1.T11 (VSS), U1.T12 (VSS), U1.U4 (VSS), U1.U8 (VSS), U1.U9 (VSS), U1.U11 (VSS), U1.U13 (VSS), U1.U14 (VSS), U1.U15 (VSS), U1.V4 (VSS), U1.V8 (VSS), U1.V11 (VSS), U1.W1 (VSS), U1.W3 (VSS), U1.W4 (VSS), U1.W5 (VSS), U1.W7 (VSS), U1.W8 (VSS), U1.W9 (VSS), U2.21 (REFGND), U2.33 (PAD); also elsewhere on the board
unnamed: D14.2 (A), R20.2
unnamed: R1.2, R2.1, U2.31 (FB3)
unnamed: C72.1, U2.32 (PWRON)
unnamed: L1.2, U2.14 (SW1)
unnamed: L2.2, U2.11 (SW2)
unnamed: L3.1, U2.30 (SW3)
unnamed: L4.1, U2.27 (SW4)
unnamed: C26.1, U2.20 (VREF)

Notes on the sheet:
Close to pins
close
>12mil (close)
Buck 3 voltage set by external resistor VBuck3Out = Vfb3 * (1 + Rfbup/Rfbdn) Vfb3 typically = 0.8v For DDR3 0.8 * (1 + 1K / 1.1K) = 1.527v

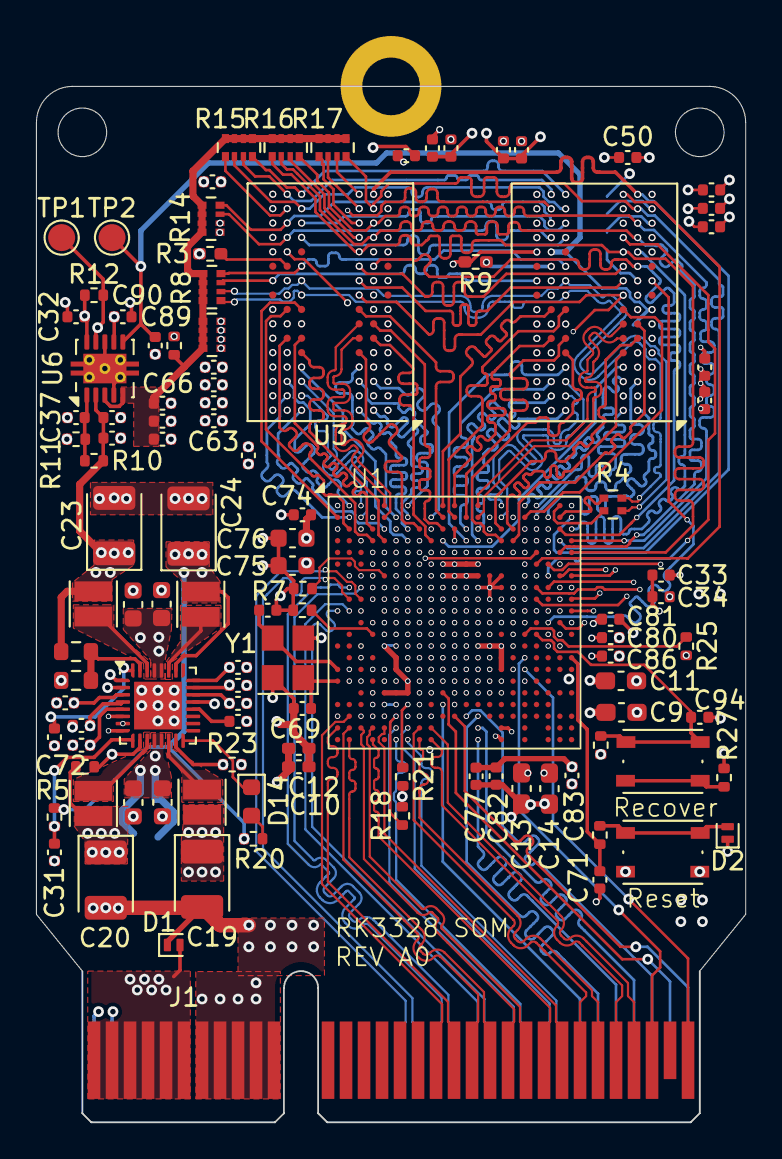
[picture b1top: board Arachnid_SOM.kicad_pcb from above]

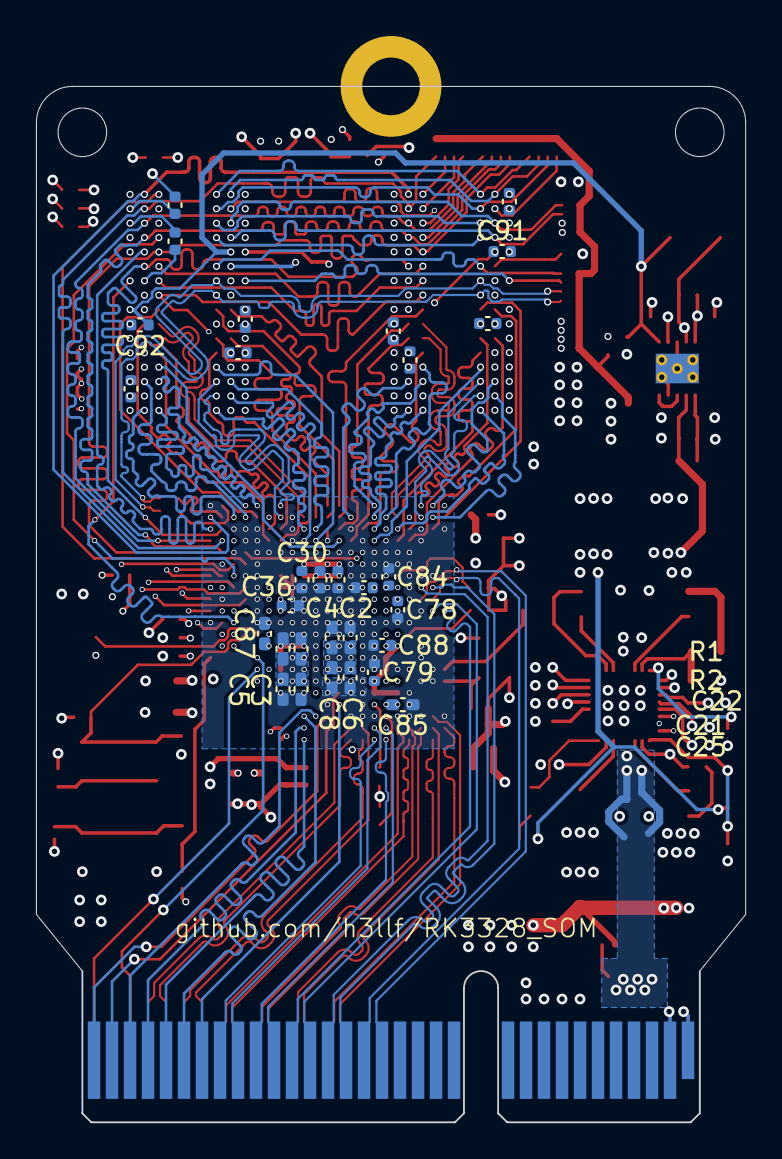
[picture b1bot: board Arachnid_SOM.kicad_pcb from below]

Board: 6 copper layers, 39.4 x 57.5 mm, 139 parts (30 on the bottom side), 147 nets.

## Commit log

2025-04-07 Initial
2025-04-07 gitignore
2025-04-10 First revision
2025-04-10 Minor changes
